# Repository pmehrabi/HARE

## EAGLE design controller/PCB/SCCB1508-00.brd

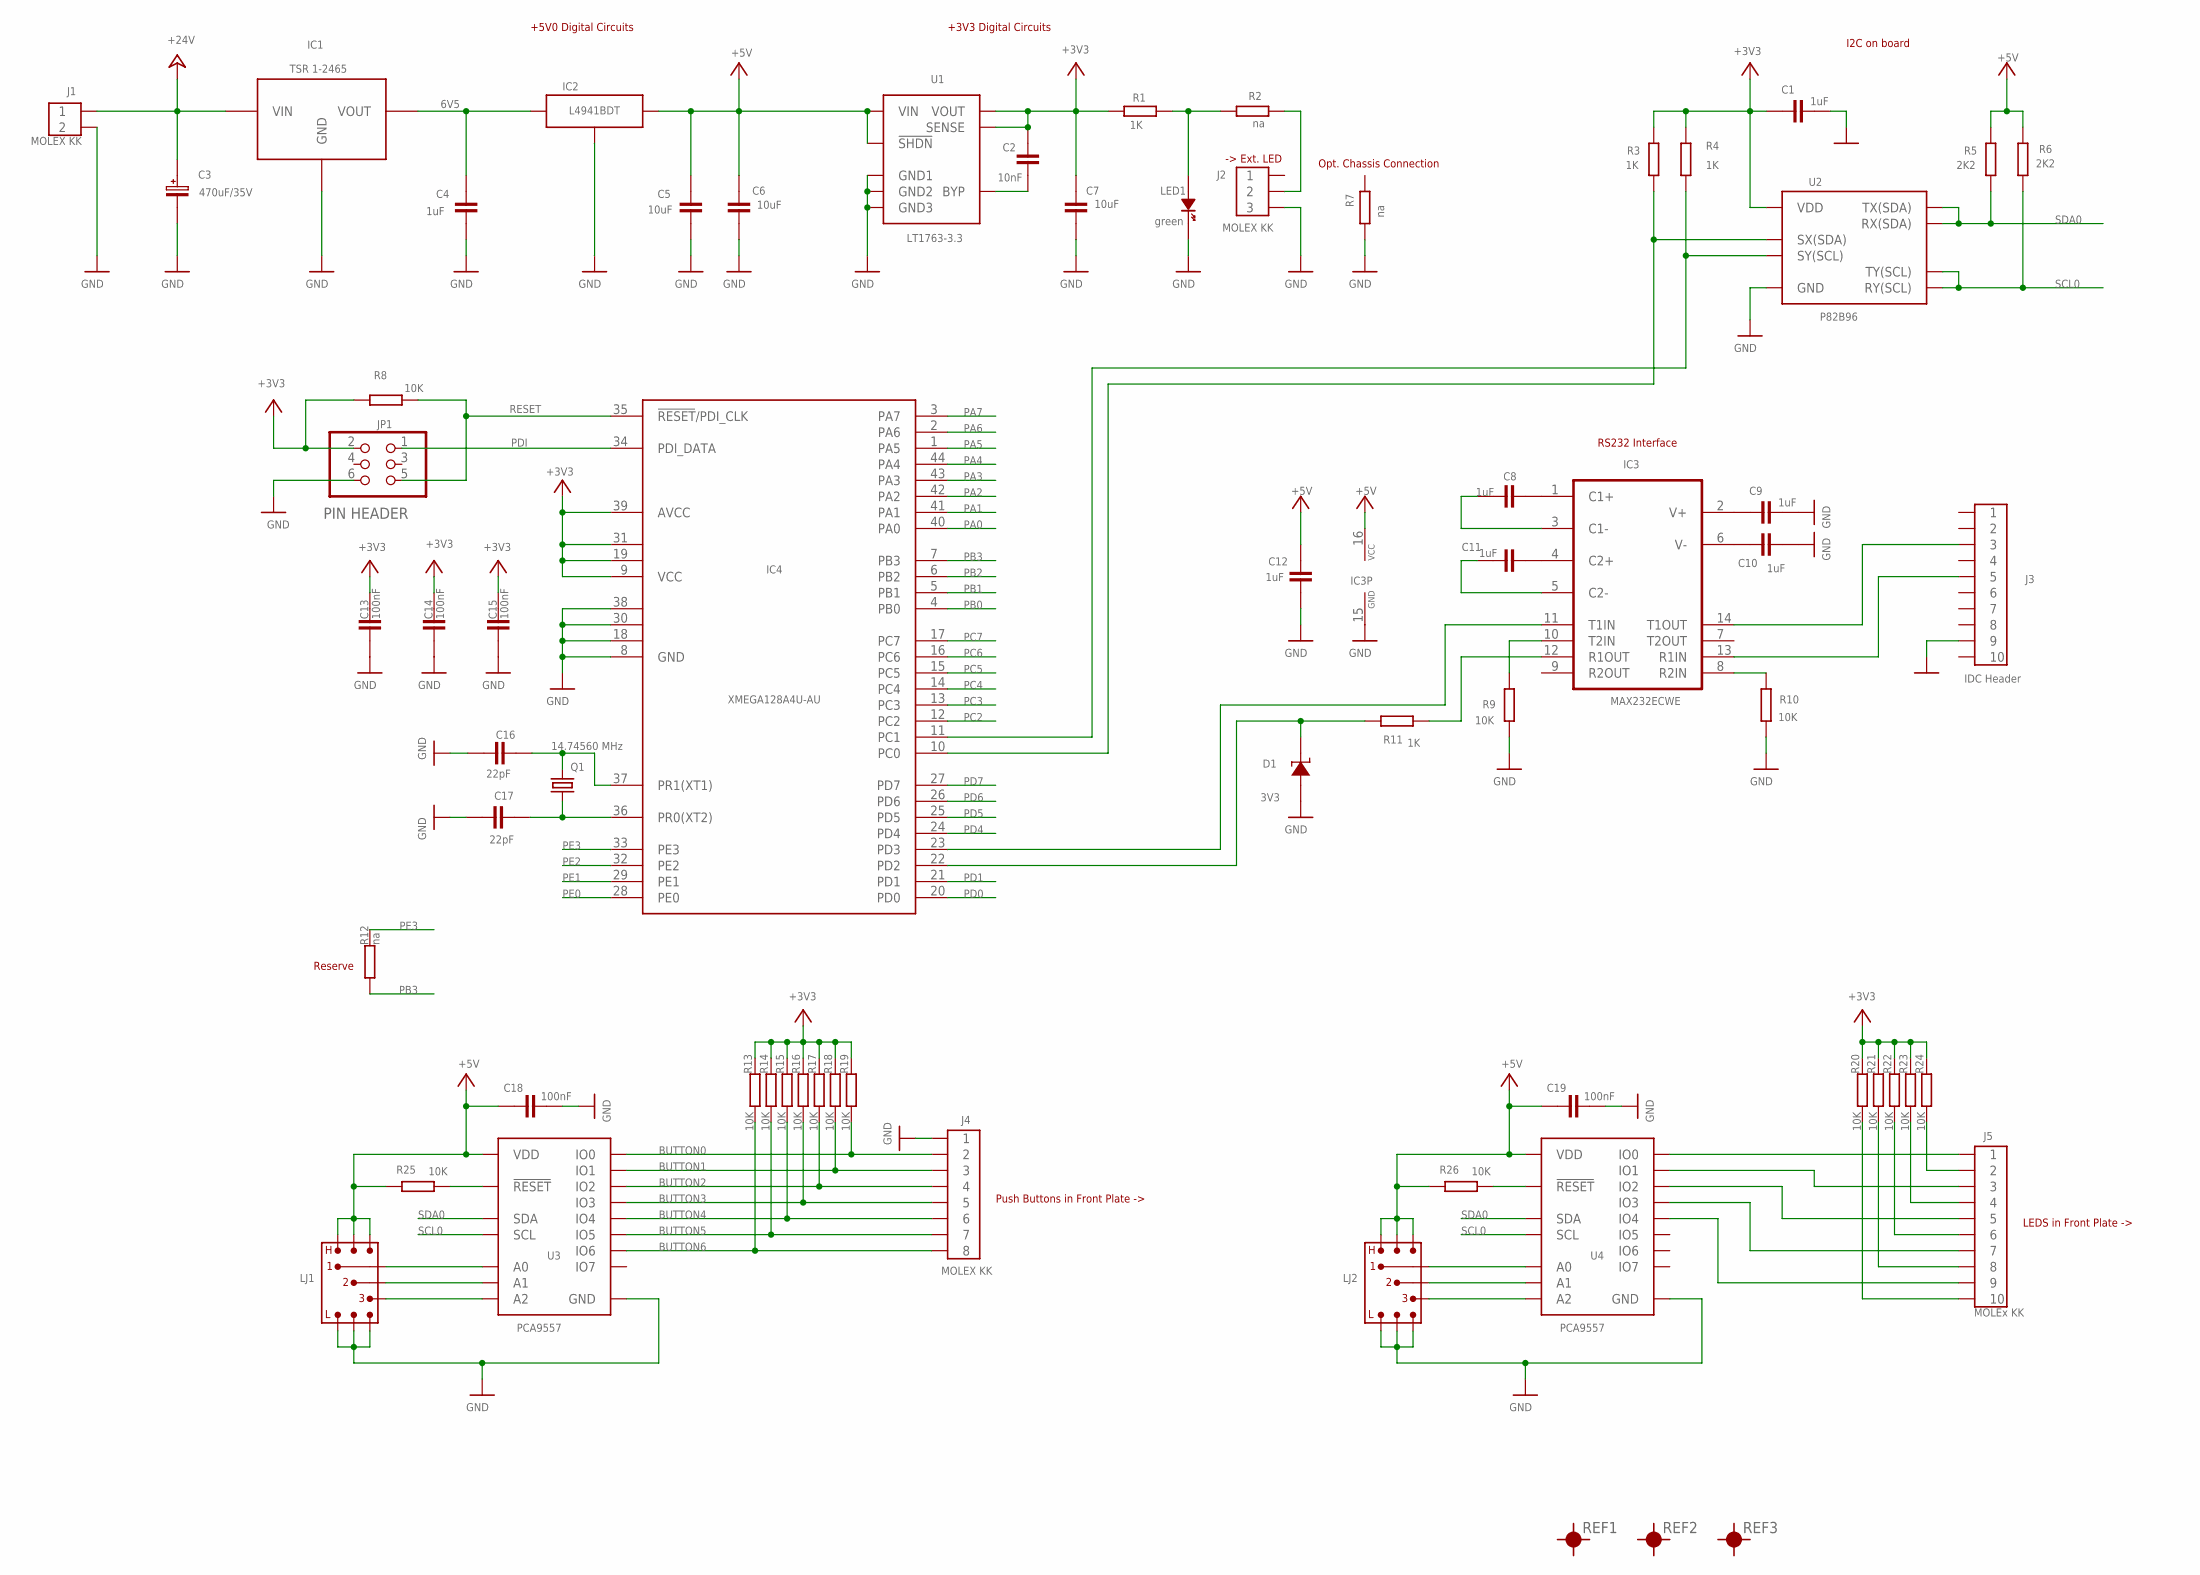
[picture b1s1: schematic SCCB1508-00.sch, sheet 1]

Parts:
C1, C4, C8, C9, C10, C11, C12: 1uF; 0805
C2: 10nF; 0603
C3: 470uF/35V; C_POL_RM5_D16
C5, C6, C7: 10uF; 1206
C13, C14, C15, C18, C19: 100nF; 0603
C16, C17: 22pF; 0603
D1: 3V3; SOT_23
IC1: TSR 1-2465; TRACO_TSR_1
IC2: L4941BDT; D_PAK
IC3: MAX232ECWE; SO16L
IC4: XMEGA128A4U-AU; TQFP44
J1: MOLEX KK; MOLEX_KK_02POL
J2: MOLEX KK; MOLEX_KK_03POL
J3: IDC Header; IDC_WANNE_10POL
J4: MOLEX KK; MOLEX_KK_08POL
J5: MOLEx KK; MOLEX_KK_10POL
JP1: PIN HEADER; 2X03
LED1: green; 0603_POL
LJ1, LJ2: LOETJUMPER_3KHL_; LOETJUMPER_3KHL
Q1: 14.74560 MHz; HC49UP
R1, R3, R4, R11: 1K; 0603
R2: na; 1206
R5, R6: 2K2; 0603
R7: na; 0603
R8, R9, R10, R13, R14, R15, R16, R17, R18, R19, R20, R21, R22, R23, R24, R25, R26: 10K; 0603
R12: na; 0805
REF1, REF2, REF3: PASSERMARKE_1.0; PASSERMARKE_01
U1: LT1763-3.3; SOIC127P-6-8POL
U2: P82B96; SO_8_BW3.9MM
U3, U4: PCA9557; SO_16_BW3.9MM

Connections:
6V5: C4.2, IC1.P$3 (VOUT), IC2.1 (IN)
+3V3: C1.1, C2.2, C7.2, C13.2, C14.2, C15.2, IC4.9 (VCC), IC4.19 (VCC1), IC4.31 (VCC2), IC4.39 (AVCC), JP1.2, R1.2, R3.1, R4.1, R8.1, R13.1, R14.1, R15.1, R16.1, R17.1, R18.1, R19.1, R20.1, R21.1, R22.1, R23.1, R24.1, U1.1 (VOUT), U1.2 (SENSE), U2.8 (VDD); also elsewhere on the board
+5V: C5.2, C6.2, C12.2, C18.2, C19.2, IC2.3 (OUT), IC3.16 (VCC), LJ1.H1, LJ1.H2, LJ1.H3, LJ2.H1, LJ2.H2, LJ2.H3, R5.1, R6.1, R25.2, R26.2, U1.5 (!SHDN), U1.8 (VIN), U3.16 (VDD), U4.16 (VDD); also elsewhere on the board
+24V: C3.1 (PLUS), IC1.P$1 (VIN), J1.P$1 (1)
BUTTON0: J4.P$2 (2), R19.2, U3.6 (IO0)
BUTTON1: J4.P$3 (3), R18.2, U3.7 (IO1)
BUTTON2: J4.P$4 (4), R17.2, U3.9 (IO2)
BUTTON3: J4.P$5 (5), R16.2, U3.10 (IO3)
BUTTON4: J4.P$6 (6), R15.2, U3.11 (IO4)
BUTTON5: J4.P$7 (7), R14.2, U3.12 (IO5)
BUTTON6: J4.P$8 (8), R13.2, U3.13 (IO6)
GND: C1.2, C3.2 (MINUS), C4.1, C5.1, C6.1, C7.1, C9.2, C10.2, C12.1, C13.1, C14.1, C15.1, C16.1, C17.1, C18.1, C19.1, D1.1 (ANODE), IC1.P$2 (GND), IC2.2 (GND), IC3.15 (GND), IC4.8 (GND), IC4.18 (GND1), IC4.30 (GND2), IC4.38 (GND3), J1.P$2 (2), J2.P$3 (3), J3.9, J4.P$1 (1), JP1.6, LED1.1 (KATHODE), LJ1.L1, LJ1.L2, LJ1.L3, LJ2.L1, LJ2.L2, LJ2.L3, R7.2, R9.1, R10.1, U1.3 (GND1), U1.6 (GND2), U1.7 (GND3), U2.4 (GND), U3.8 (GND), U4.8 (GND); also elsewhere on the board
unnamed: C8.1, IC3.1 (C1+)
unnamed: IC3.14 (T1OUT), J3.3
unnamed: C9.1, IC3.2 (V+)
unnamed: IC3.10 (T2IN), R9.2
unnamed: C10.1, IC3.6 (V-)
unnamed: C11.1, IC3.4 (C2+)
unnamed: C8.2, IC3.3 (C1-)
unnamed: IC3.8 (R2IN), R10.2
unnamed: C11.2, IC3.5 (C2-)
unnamed: C2.1, U1.4 (BYP)
unnamed: LED1.2 (ANODE), R1.1, R2.1
unnamed: J2.P$2 (2), R2.2
unnamed: C16.2, IC4.37 (PR1(XT1)), Q1.1
unnamed: C17.2, IC4.36 (PR0(XT2)), Q1.2
unnamed: IC3.12 (R1OUT), R11.2
unnamed: J5.P$2 (2), R24.2
unnamed: J5.P$4 (4), R23.2
unnamed: J5.P$6 (6), R22.2
unnamed: J5.P$8 (8), R21.2
unnamed: IC3.13 (R1IN), J3.5
unnamed: J5.P$10 (10), R20.2
unnamed: R25.1, U3.15 (!RESET)
unnamed: LJ2.1, U4.3 (A0)
unnamed: LJ2.2, U4.4 (A1)
unnamed: LJ2.3, U4.5 (A2)
unnamed: R26.1, U4.15 (!RESET)
unnamed: LJ1.1, U3.3 (A0)
unnamed: LJ1.2, U3.4 (A1)
unnamed: LJ1.3, U3.5 (A2)
unnamed: IC4.11 (PC1), R4.2, U2.7 (SY(SCL))
unnamed: IC4.10 (PC0), R3.2, U2.1 (SX(SDA))
unnamed: J5.P$1 (1), U4.6 (IO0)
unnamed: J5.P$3 (3), U4.7 (IO1)
unnamed: J5.P$5 (5), U4.9 (IO2)
unnamed: J5.P$7 (7), U4.10 (IO3)
unnamed: J5.P$9 (9), U4.11 (IO4)
PA0: IC4.40 (PA0); also elsewhere on the board
PA1: IC4.41 (PA1); also elsewhere on the board
PA2: IC4.42 (PA2); also elsewhere on the board
PA3: IC4.43 (PA3); also elsewhere on the board
PA4: IC4.44 (PA4); also elsewhere on the board
PA5: IC4.1 (PA5); also elsewhere on the board
PA6: IC4.2 (PA6); also elsewhere on the board
PA7: IC4.3 (PA7); also elsewhere on the board
PB0: IC4.4 (PB0); also elsewhere on the board
PB1: IC4.5 (PB1); also elsewhere on the board
PB2: IC4.6 (PB2); also elsewhere on the board
PB3: IC4.7 (PB3), R12.1
PC2: IC4.12 (PC2); also elsewhere on the board
PC3: IC4.13 (PC3); also elsewhere on the board
PC4: IC4.14 (PC4); also elsewhere on the board
PC5: IC4.15 (PC5); also elsewhere on the board
PC6: IC4.16 (PC6); also elsewhere on the board
PC7: IC4.17 (PC7); also elsewhere on the board
PD0: IC4.20 (PD0); also elsewhere on the board
PD1: IC4.21 (PD1); also elsewhere on the board
PD4: IC4.24 (PD4); also elsewhere on the board
PD5: IC4.25 (PD5); also elsewhere on the board
PD6: IC4.26 (PD6); also elsewhere on the board
PD7: IC4.27 (PD7); also elsewhere on the board
PDI: IC4.34 (PDI_DATA), JP1.1
PE0: IC4.28 (PE0); also elsewhere on the board
PE1: IC4.29 (PE1); also elsewhere on the board
PE2: IC4.32 (PE2); also elsewhere on the board
PE3: IC4.33 (PE3), R12.2
RESET: IC4.35 (!RESET!/PDI_CLK), JP1.5, R8.2
RX0: D1.3 (KATHODE), IC4.22 (PD2), R11.1
SCL0: R6.2, U2.5 (TY(SCL)), U2.6 (RY(SCL)), U3.1 (SCL), U4.1 (SCL); also elsewhere on the board
SDA0: R5.2, U2.2 (RX(SDA)), U2.3 (TX(SDA)), U3.2 (SDA), U4.2 (SDA); also elsewhere on the board
TX0: IC3.11 (T1IN), IC4.23 (PD3)

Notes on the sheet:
RS232 Interface
+3V3 Digital Circuits
+5V0 Digital Circuits
-> Ext. LED
Push Buttons in Front Plate ->
LEDS in Front Plate ->
I2C on board
Reserve
Opt. Chassis Connection

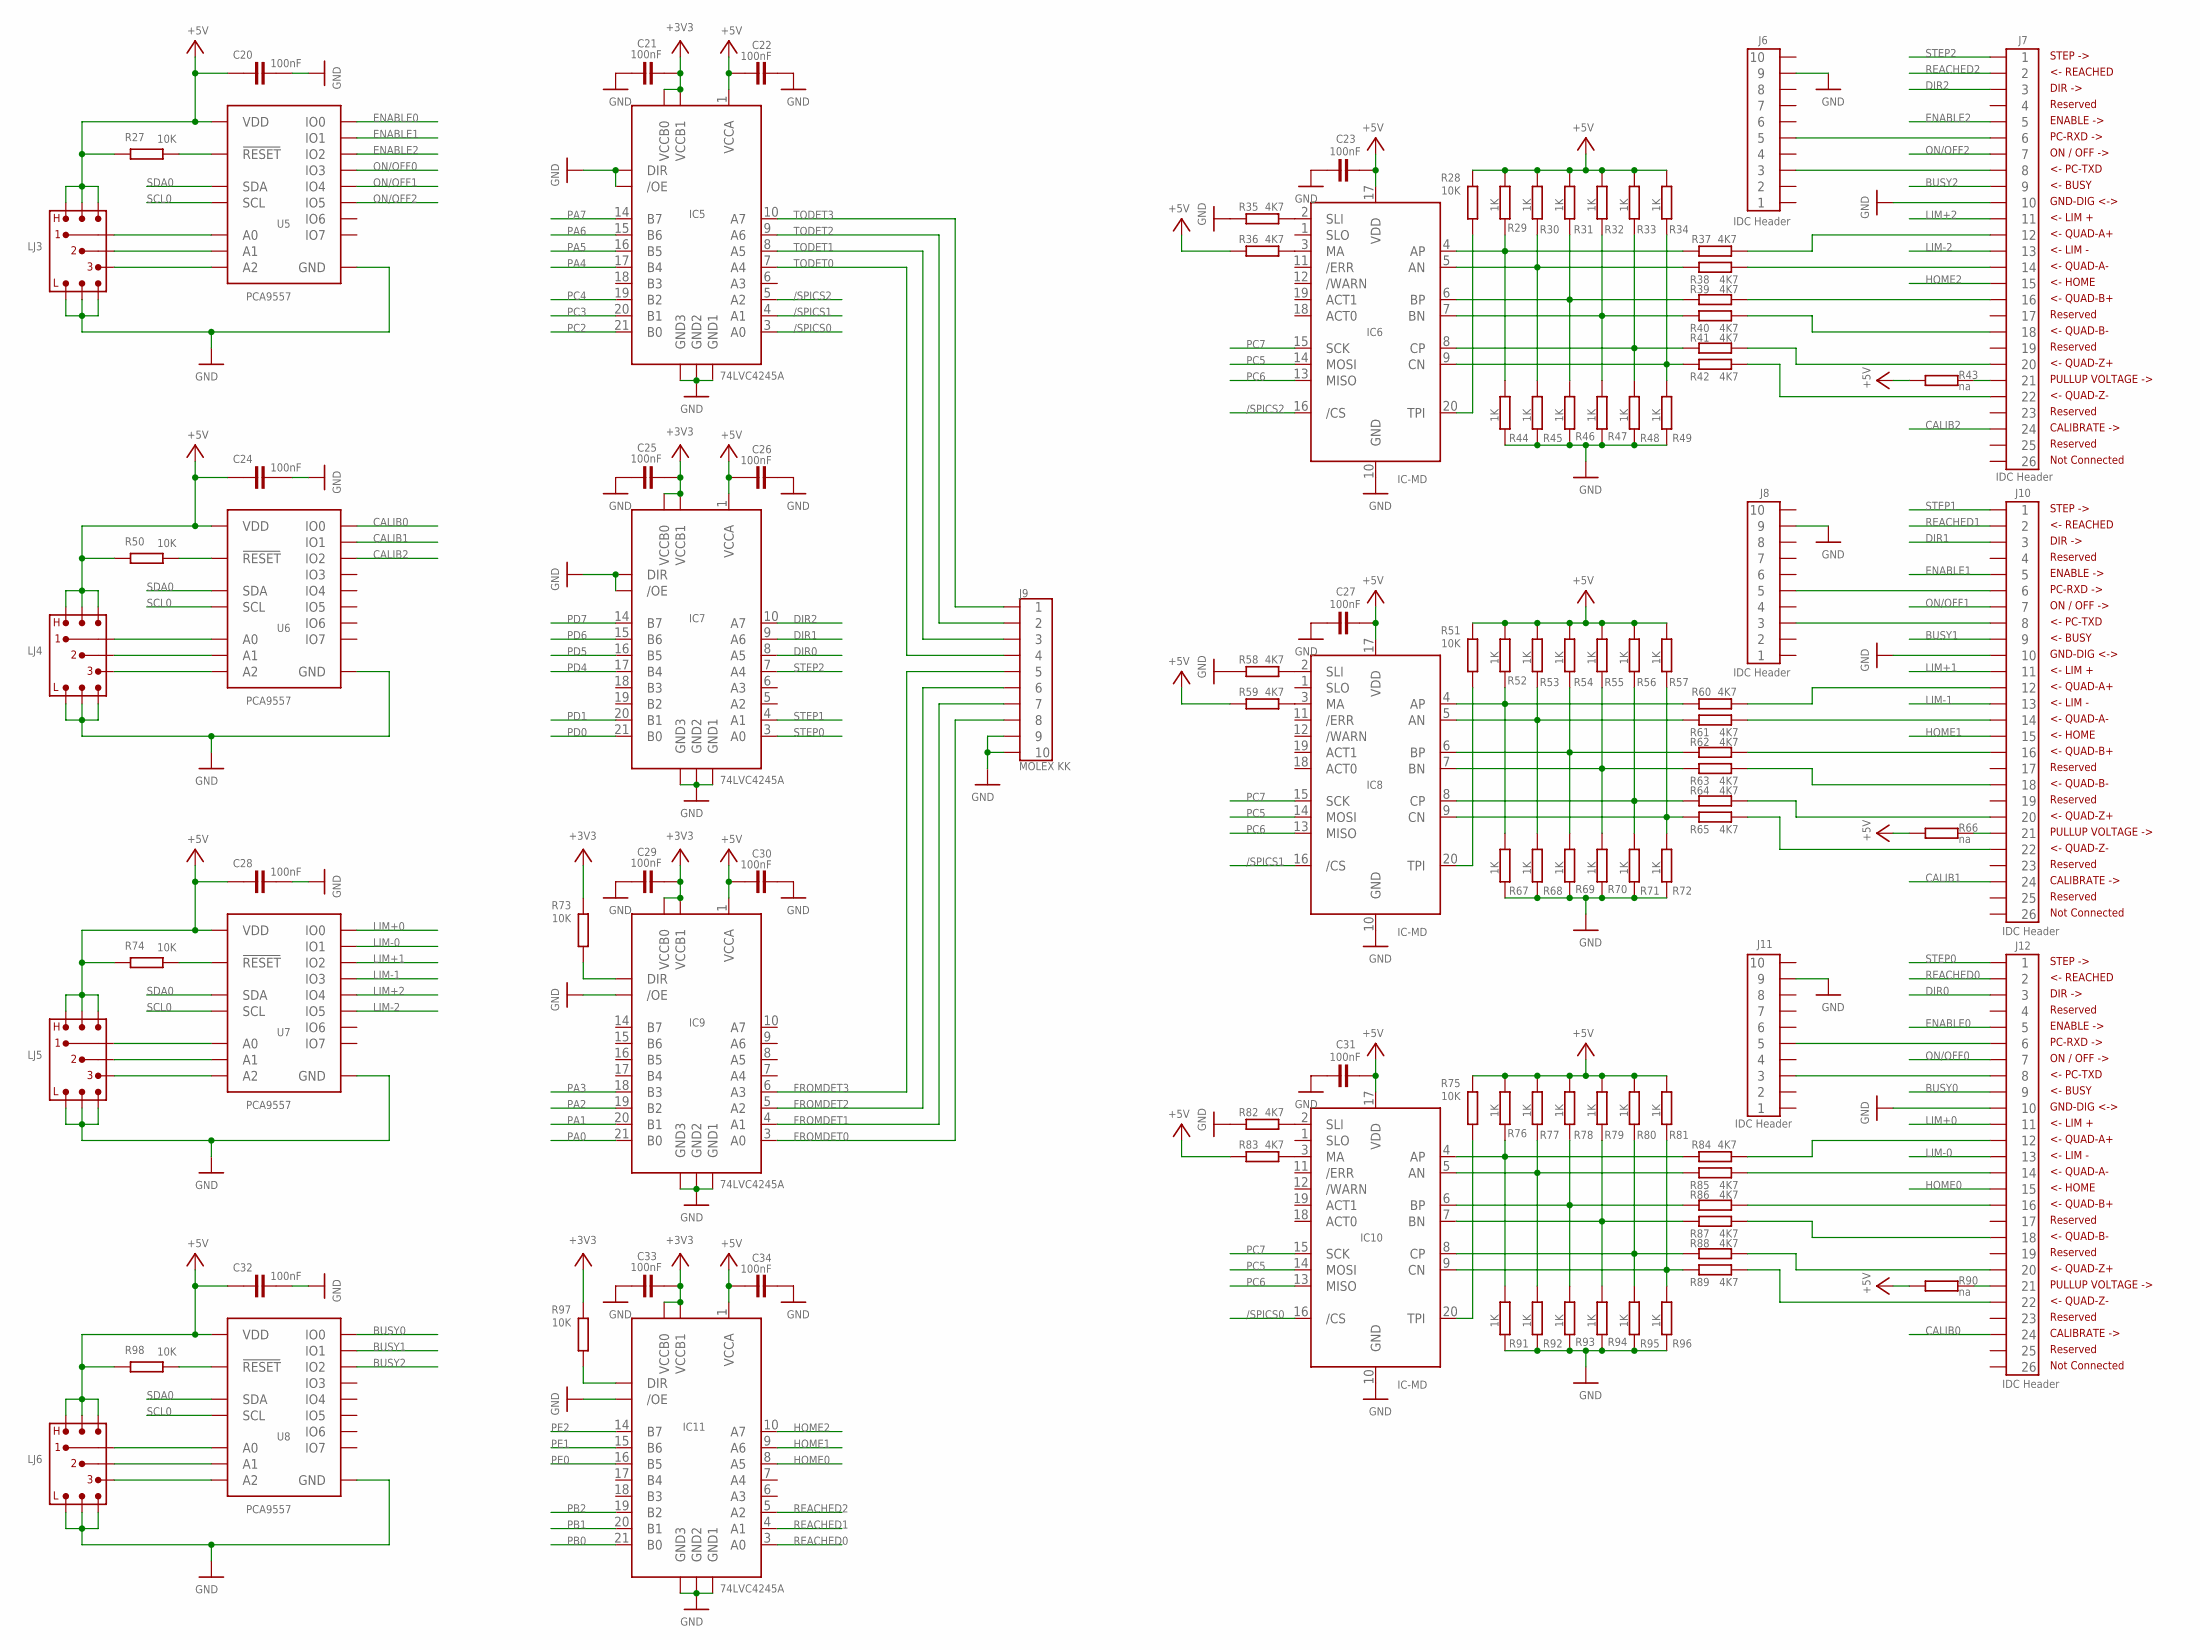
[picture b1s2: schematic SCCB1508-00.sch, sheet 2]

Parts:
C20, C21, C22, C23, C24, C25, C26, C27, C28, C29, C30, C31, C32, C33, C34: 100nF; 0603
IC5, IC7, IC9, IC11: 74LVC4245A; SO_24_BW5.3MM
IC6, IC8, IC10: IC-MD; SSOP_20_BW4.4
J6, J8, J11: IDC Header; IDC_WANNE_10POL
J7, J10, J12: IDC Header; IDC_WANNE_26POL
J9: MOLEX KK; MOLEX_KK_10POL
LJ3, LJ4, LJ5, LJ6: LOETJUMPER_3KHL_; LOETJUMPER_3KHL
R27, R28, R50, R51, R73, R74, R75, R97, R98: 10K; 0603
R29, R30, R31, R32, R33, R34, R44, R45, R46, R47, R48, R49, R52, R53, R54, R55, R56, R57, R67, R68, R69, R70, R71, R72, R76, R77, R78, R79, R80, R81, R91, R92, R93, R94, R95, R96: 1K; 0603
R35, R36, R37, R38, R39, R40, R41, R42, R58, R59, R60, R61, R62, R63, R64, R65, R82, R83, R84, R85, R86, R87, R88, R89: 4K7; 0603
R43, R66, R90: na; RM10L10B2.5
U5, U6, U7, U8: PCA9557; SO_16_BW3.9MM

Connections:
+3V3: C21.1, C25.1, C29.1, C33.1, IC5.23 (VCCB0), IC5.24 (VCCB1), IC7.23 (VCCB0), IC7.24 (VCCB1), IC9.23 (VCCB0), IC9.24 (VCCB1), IC11.23 (VCCB0), IC11.24 (VCCB1), R73.1, R97.1; also elsewhere on the board
+5V: C20.2, C22.2, C23.2, C24.2, C26.2, C27.2, C28.2, C30.2, C31.2, C32.2, C34.2, IC5.1 (VCCA), IC6.17 (VDD), IC7.1 (VCCA), IC8.17 (VDD), IC9.1 (VCCA), IC10.17 (VDD), IC11.1 (VCCA), LJ3.H1, LJ3.H2, LJ3.H3, LJ4.H1, LJ4.H2, LJ4.H3, LJ5.H1, LJ5.H2, LJ5.H3, LJ6.H1, LJ6.H2, LJ6.H3, R27.2, R28.1, R29.2, R30.2, R31.2, R32.2, R33.2, R34.2, R36.1, R43.1, R50.2, R51.1, R52.2, R53.2, R54.2, R55.2, R56.2, R57.2, R59.1, R66.1, R74.2, R75.1, R76.2, R77.2, R78.2, R79.2, R80.2, R81.2, R83.1, R90.1, R98.2, U5.16 (VDD), U6.16 (VDD), U7.16 (VDD), U8.16 (VDD); also elsewhere on the board
/SPICS0: IC5.3 (A0), IC10.16 (/CS)
/SPICS1: IC5.4 (A1), IC8.16 (/CS)
/SPICS2: IC5.5 (A2), IC6.16 (/CS)
BUSY0: J12.9, U8.6 (IO0)
BUSY1: J10.9, U8.7 (IO1)
BUSY2: J7.9, U8.9 (IO2)
CALIB0: J12.24, U6.6 (IO0)
CALIB1: J10.24, U6.7 (IO1)
CALIB2: J7.24, U6.9 (IO2)
DIR0: IC7.8 (A5), J12.3
DIR1: IC7.9 (A6), J10.3
DIR2: IC7.10 (A7), J7.3
ENABLE0: J12.5, U5.6 (IO0)
ENABLE1: J10.5, U5.7 (IO1)
ENABLE2: J7.5, U5.9 (IO2)
FROMDET0: IC9.3 (A0), J9.P$8 (8)
FROMDET1: IC9.4 (A1), J9.P$7 (7)
FROMDET2: IC9.5 (A2), J9.P$6 (6)
FROMDET3: IC9.6 (A3), J9.P$5 (5)
GND: C20.1, C21.2, C22.1, C23.1, C24.1, C25.2, C26.1, C27.1, C28.1, C29.2, C30.1, C31.1, C32.1, C33.2, C34.1, IC5.2 (DIR), IC5.11 (GND1), IC5.12 (GND2), IC5.13 (GND3), IC5.22 (/OE), IC6.10 (GND), IC7.2 (DIR), IC7.11 (GND1), IC7.12 (GND2), IC7.13 (GND3), IC7.22 (/OE), IC8.10 (GND), IC9.11 (GND1), IC9.12 (GND2), IC9.13 (GND3), IC9.22 (/OE), IC10.10 (GND), IC11.11 (GND1), IC11.12 (GND2), IC11.13 (GND3), IC11.22 (/OE), J6.9, J7.10, J8.9, J9.P$9 (9), J9.P$10 (10), J10.10, J11.9, J12.10, LJ3.L1, LJ3.L2, LJ3.L3, LJ4.L1, LJ4.L2, LJ4.L3, LJ5.L1, LJ5.L2, LJ5.L3, LJ6.L1, LJ6.L2, LJ6.L3, R35.1, R44.1, R45.1, R46.1, R47.1, R48.1, R49.1, R58.1, R67.1, R68.1, R69.1, R70.1, R71.1, R72.1, R82.1, R91.1, R92.1, R93.1, R94.1, R95.1, R96.1, U5.8 (GND), U6.8 (GND), U7.8 (GND), U8.8 (GND); also elsewhere on the board
HOME0: IC11.8 (A5), J12.15
HOME1: IC11.9 (A6), J10.15
HOME2: IC11.10 (A7), J7.15
LIM+0: J12.11, U7.6 (IO0)
LIM+1: J10.11, U7.9 (IO2)
LIM+2: J7.11, U7.11 (IO4)
LIM-0: J12.13, U7.7 (IO1)
LIM-1: J10.13, U7.10 (IO3)
LIM-2: J7.13, U7.12 (IO5)
unnamed: J6.3, J7.8
unnamed: J6.5, J7.6
unnamed: IC6.20 (TPI), R28.2
unnamed: IC6.9 (CN), R34.1, R42.1, R49.2
unnamed: IC6.8 (CP), R33.1, R41.1, R48.2
unnamed: IC6.7 (BN), R32.1, R40.1, R47.2
unnamed: IC6.6 (BP), R31.1, R39.1, R46.2
unnamed: IC6.5 (AN), R30.1, R38.1, R45.2
unnamed: IC6.4 (AP), R29.1, R37.1, R44.2
unnamed: IC6.3 (MA), R36.2
unnamed: IC6.2 (SLI), R35.2
unnamed: J7.12, R37.2
unnamed: J7.14, R38.2
unnamed: J7.16, R39.2
unnamed: J7.18, R40.2
unnamed: J7.20, R41.2
unnamed: J7.22, R42.2
unnamed: IC9.2 (DIR), R73.2
unnamed: IC11.2 (DIR), R97.2
unnamed: LJ5.1, U7.3 (A0)
unnamed: LJ5.2, U7.4 (A1)
unnamed: J7.21, R43.2
unnamed: LJ5.3, U7.5 (A2)
unnamed: R74.1, U7.15 (!RESET)
unnamed: LJ3.1, U5.3 (A0)
unnamed: LJ3.2, U5.4 (A1)
unnamed: LJ3.3, U5.5 (A2)
unnamed: R27.1, U5.15 (!RESET)
unnamed: LJ4.1, U6.3 (A0)
unnamed: LJ4.2, U6.4 (A1)
unnamed: LJ4.3, U6.5 (A2)
unnamed: R50.1, U6.15 (!RESET)
unnamed: LJ6.1, U8.3 (A0)
unnamed: LJ6.2, U8.4 (A1)
unnamed: LJ6.3, U8.5 (A2)
unnamed: R98.1, U8.15 (!RESET)
unnamed: J8.3, J10.8
unnamed: J8.5, J10.6
unnamed: IC8.9 (CN), R57.1, R65.1, R72.2
unnamed: IC8.8 (CP), R56.1, R64.1, R71.2
unnamed: IC8.7 (BN), R55.1, R63.1, R70.2
unnamed: IC8.6 (BP), R54.1, R62.1, R69.2
unnamed: IC8.5 (AN), R53.1, R61.1, R68.2
unnamed: IC8.4 (AP), R52.1, R60.1, R67.2
unnamed: IC8.20 (TPI), R51.2
unnamed: IC8.3 (MA), R59.2
unnamed: IC8.2 (SLI), R58.2
unnamed: J10.12, R60.2
unnamed: J10.14, R61.2
unnamed: J10.16, R62.2
unnamed: J10.18, R63.2
unnamed: J10.20, R64.2
unnamed: J10.22, R65.2
unnamed: J10.21, R66.2
unnamed: J11.3, J12.8
unnamed: J11.5, J12.6
unnamed: IC10.9 (CN), R81.1, R89.1, R96.2
unnamed: IC10.8 (CP), R80.1, R88.1, R95.2
unnamed: IC10.7 (BN), R79.1, R87.1, R94.2
unnamed: IC10.6 (BP), R78.1, R86.1, R93.2
unnamed: IC10.5 (AN), R77.1, R85.1, R92.2
unnamed: IC10.4 (AP), R76.1, R84.1, R91.2
unnamed: IC10.20 (TPI), R75.2
unnamed: IC10.3 (MA), R83.2
unnamed: IC10.2 (SLI), R82.2
unnamed: J12.12, R84.2
unnamed: J12.14, R85.2
unnamed: J12.16, R86.2
unnamed: J12.18, R87.2
unnamed: J12.20, R88.2
unnamed: J12.22, R89.2
unnamed: J12.21, R90.2
ON/OFF0: J12.7, U5.10 (IO3)
ON/OFF1: J10.7, U5.11 (IO4)
ON/OFF2: J7.7, U5.12 (IO5)
PA0: IC9.21 (B0); also elsewhere on the board
PA1: IC9.20 (B1); also elsewhere on the board
PA2: IC9.19 (B2); also elsewhere on the board
PA3: IC9.18 (B3); also elsewhere on the board
PA4: IC5.17 (B4); also elsewhere on the board
PA5: IC5.16 (B5); also elsewhere on the board
PA6: IC5.15 (B6); also elsewhere on the board
PA7: IC5.14 (B7); also elsewhere on the board
PB0: IC11.21 (B0); also elsewhere on the board
PB1: IC11.20 (B1); also elsewhere on the board
PB2: IC11.19 (B2); also elsewhere on the board
PC2: IC5.21 (B0); also elsewhere on the board
PC3: IC5.20 (B1); also elsewhere on the board
PC4: IC5.19 (B2); also elsewhere on the board
PC5: IC6.14 (MOSI), IC8.14 (MOSI), IC10.14 (MOSI); also elsewhere on the board
PC6: IC6.13 (MISO), IC8.13 (MISO), IC10.13 (MISO); also elsewhere on the board
PC7: IC6.15 (SCK), IC8.15 (SCK), IC10.15 (SCK); also elsewhere on the board
PD0: IC7.21 (B0); also elsewhere on the board
PD1: IC7.20 (B1); also elsewhere on the board
PD4: IC7.17 (B4); also elsewhere on the board
PD5: IC7.16 (B5); also elsewhere on the board
PD6: IC7.15 (B6); also elsewhere on the board
PD7: IC7.14 (B7); also elsewhere on the board
PE0: IC11.16 (B5); also elsewhere on the board
PE1: IC11.15 (B6); also elsewhere on the board
PE2: IC11.14 (B7); also elsewhere on the board
REACHED0: IC11.3 (A0), J12.2
REACHED1: IC11.4 (A1), J10.2
REACHED2: IC11.5 (A2), J7.2
SCL0: U5.1 (SCL), U6.1 (SCL), U7.1 (SCL), U8.1 (SCL); also elsewhere on the board
SDA0: U5.2 (SDA), U6.2 (SDA), U7.2 (SDA), U8.2 (SDA); also elsewhere on the board
STEP0: IC7.3 (A0), J12.1
STEP1: IC7.4 (A1), J10.1
STEP2: IC7.7 (A4), J7.1
TODET0: IC5.7 (A4), J9.P$4 (4)
TODET1: IC5.8 (A5), J9.P$3 (3)
TODET2: IC5.9 (A6), J9.P$2 (2)
TODET3: IC5.10 (A7), J9.P$1 (1)

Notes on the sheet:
GND-DIG <->
STEP ->
DIR ->
ENABLE ->
ON / OFF ->
<- BUSY
<- LIM +
<- LIM -
<- HOME
Reserved
PULLUP VOLTAGE ->
<- REACHED
PC-RXD ->
<- PC-TXD
<- QUAD-A+
<- QUAD-A-
<- QUAD-B+
<- QUAD-B-
<- QUAD-Z+
<- QUAD-Z-
CALIBRATE ->
Not Connected

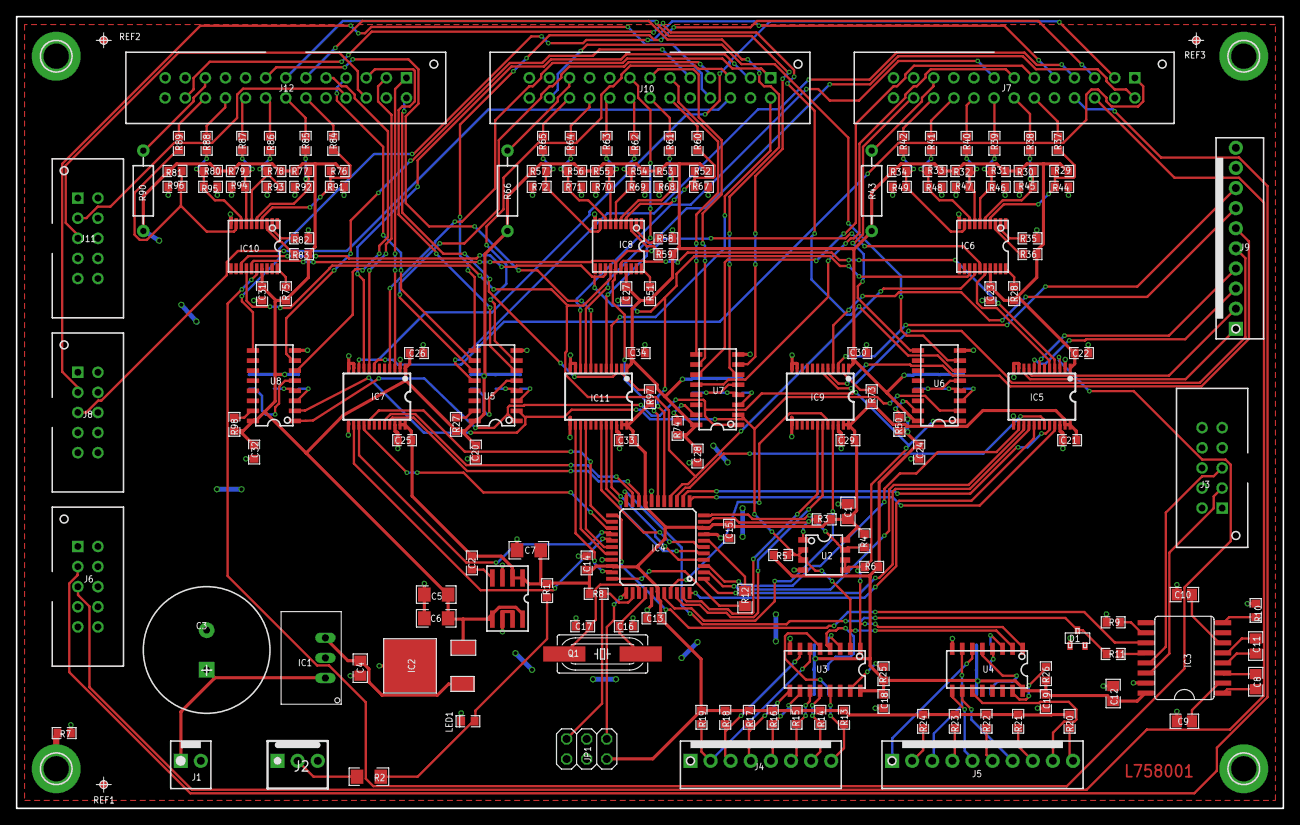
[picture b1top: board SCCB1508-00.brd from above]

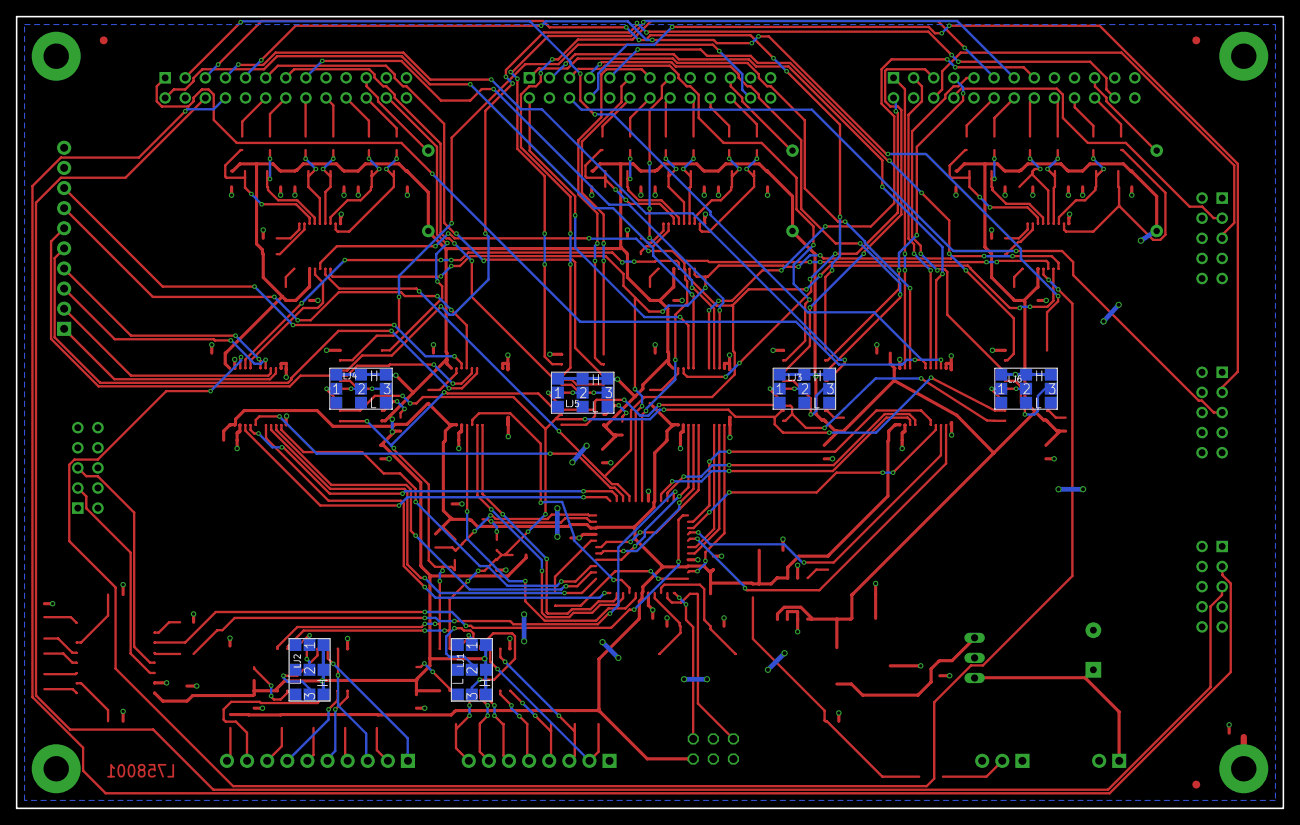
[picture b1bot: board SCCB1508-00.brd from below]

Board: 2 copper layers, 160.0 x 100.0 mm, 176 parts (6 on the bottom side), 195 nets.

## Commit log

2018-08-08 Add files via upload
    Controller Files
2018-08-08 Add files via upload
    LabVIEW GUI
